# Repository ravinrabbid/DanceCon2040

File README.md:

# DanceCon2040 - A RP2040 based Dance Pad

DanceCon2040 is a firmware (and by extension a PCB) for arcade style Dance Pad controllers with up to nine panels.

It is pretty much tailored to this specific use case, if you are looking for something universal, ready-to-flash and on-the-fly configurable I'd recommend to have a look at more generic approaches like [GP2040-CE](https://github.com/OpenStickCommunity/GP2040-CE). If you however want build something more specialized or custom, feel free to use this project as a base, it is designed to be somewhat modular and should be easy remodel. See [DivaCon2040](https://github.com/ravinrabbid/DivaCon2040) or [DonCon2040](https://github.com/ravinrabbid/DonCon2040) for examples on how this could look like.
If you have any questions about the project in general or need hints how to build this thing, feel free to open a [discussion](https://github.com/ravinrabbid/DanceCon2040/discussions) anytime!

## Features

- Various controller emulation modes
  - Spice2x - Basic USB gamepad with support for HID lights
  - Xbox360 DDR - Emulates a Xbox360 DDR Dance Mat (untested!)
  - Xbox360
  - PS3 DDR - Emulates a Playstation 3 DDR Dance Mat
  - Dualshock 3
  - Dualshock 4 (Only for PC/Steam, does not work on an actual PS4!)
  - PS4 Compat - Works on PS4 (see [PS4 Authentication](#ps4-authentication) for details)
  - Switch Pro Controller
  - Keyboard - Two different mappings for player 1 or 2 available
  - Debug mode - Outputs current state via USB serial and allows direct flashing
- Support for either 4,5,6,8 or 9 panels for different games/game modes.
- Additional buttons via external i2c GPIO expander
- Basic configuration via on-screen menu on attached OLED screen
- WS2812 LED for panel illumination
- Steps-per-minute counter counter on display

## Building

<!-- I highly recommend to build the firmware yourself so you can make adjustments in `include/GlobalConfiguration.h` to match your specific controller build.
You can still use the [binary release](https://github.com/ravinrabbid/DanceCon2040/releases) which is pre-configured for the [DanceConIO](/pcb/DanceConIO). -->

### VSCode (Windows, Linux, MacOS)

Install [VSCode](https://code.visualstudio.com/) and get the [Raspberry Pi Pico](https://marketplace.visualstudio.com/items?itemName=raspberry-pi.raspberry-pi-pico) extension. From the extension choose 'Import Project' and select the folder where you've checked out this repository, then use 'Compile Project'.

### CLI

See [pico-sdk readme](https://github.com/raspberrypi/pico-sdk/blob/master/README.md#quick-start-your-own-project) for a list of pre-requisites.

Use the environment variables `PICO_SDK_PATH` to use a local pico-sdk, and `PICO_BOARD` to select another target board.
By default the pico-sdk will be fetched from Github and the target board will be "pico".

```sh
mkdir build && cd build
cmake ..
make
```

## Configuration

Few things which you probably want to change more regularly can be changed using an on-screen menu on the attached OLED display, hold both Start and Select for 2 seconds to enter the menu:

- Controller emulation mode
- Trigger thresholds
- Hold Time
- Hysteresis
- Calibration
- LED brightness, animation style and colors
- Reset settings to defaults
- Enter BOOTSEL mode for firmware flashing

Those settings are persisted to flash memory if you choose 'Save' when exiting the Menu and will survive power cycles.

Defaults and everything else is compiled statically into the firmware. You can find everything in `include/GlobalConfiguration.h`. This covers default controller emulation mode, i2c pins, ADC configuration, default trigger thresholds, hysteresis, debounce delay, panel mapping, LED colors and brightness.

### Debounce Delay / Hold Time / Hysteresis

The debounce delay also implicitly serves as the hold time of the input after a panel if triggered. On some platforms inputs won't be registered properly if this time is too short.
If you notice dropped inputs even if the controller signals an input on the LED/Display, try to increase this value.

Since the values read from load cells are not very stable, rapid triggering can happen right at the threshold value. If you encounter this, try to increase the hysteresis offset.
A panel will trigger if its value exceeds `threshold + hysteresis` and will un-trigger if its value drops below `thresholds - hysteresis` again.

### PS4 Authentication

The PS4 needs a controller to sign a cryptographic challenge every few seconds, otherwise it will stop working after around 8 minutes after plugging in. For rhythm games this is somewhat bearable, since you can re-plug the controller before starting each song to avoid running into the timeout during gameplay. Still, this is annoying.

DanceCon2040 can sign those challenges, but you will need to obtain some data from an original DS4 and compile it into the firmware. You will need a serial, signature and private key file. I can't and won't help you how to obtain those, you'll need to figure this out yourself.

To build the firmware run `scripts/generateAuthConfig.py` in the folder where you placed the required files. Copy the resulting `PS4AuthConfiguration.h` to the `include` directory, replacing the existing header. Then build the firmware as described in [Building](#building).

Signing the challenge will block the second core of the rp2040 for 2-3 seconds, so the display, external controller and LED will appear stuck from time to time. Input handling of the drum is unaffected.

## Hardware

### IO Board

The [DanceConIO](/pcb/DanceConIO) board in the pcb subfolder is built to be used with Wheatstone Bridge type panel sensors, e.g. load cells. It hosts a Waveshare RP2040-Zero and two or three ADS124S06 ADCs for up to nine differential inputs. See its [README](/pcb/DanceConIO/README.md) for details.

If you don't want to use this board, the firmware should be usable on most RP2040 boards with appropriate configuration. You may also use a more simple panel trigger solution, the firmware can also be configured to use the RP2040's internal ADC or simple GPIO style inputs.

### Controller Buttons and Display

Additional controller buttons and the display are attached to the same i2c bus. For the display, use a standard SSD1306 OLED display with 128x64 resolution. The buttons need to be attached to a MCP23017 IO expander.

See [DonConPad](/pcb/DonConPad/) for a exemplary gamepad pcb.

## Acknowledgements

- [daschr](https://github.com/daschr) for the [SSD1306 OLED driver](https://github.com/daschr/pico-ssd1306)
- [FeralAI](https://github.com/FeralAI) for the inspiration and Dualshock3/XInput driver from the [GP2040 Project](https://github.com/FeralAI/GP2040)
- The linux kernel contributors for documenting the game controllers in their drivers

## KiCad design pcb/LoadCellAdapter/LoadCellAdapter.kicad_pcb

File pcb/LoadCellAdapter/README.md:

# LoadCellAdapter

A simple passive adapter pcb to combine four 3-Wire half bridge load cells into a Wheatstone bridge configuration.

## Bill of Materials

| **Reference**      |      **Description**      | **Digikey Part** |                                                  **Notes**                                                   |
| ------------------ | :-----------------------: | :--------------: | :----------------------------------------------------------------------------------------------------------: |
| J1, J2, J3, J4, J5 | 4Pin S4B-PH-K-S Connector |   455-1721-ND    | Optional, wires can also be soldered directly to the board.</br>PHR-4 plus SPH-002T-P0.5L is the counterpart |

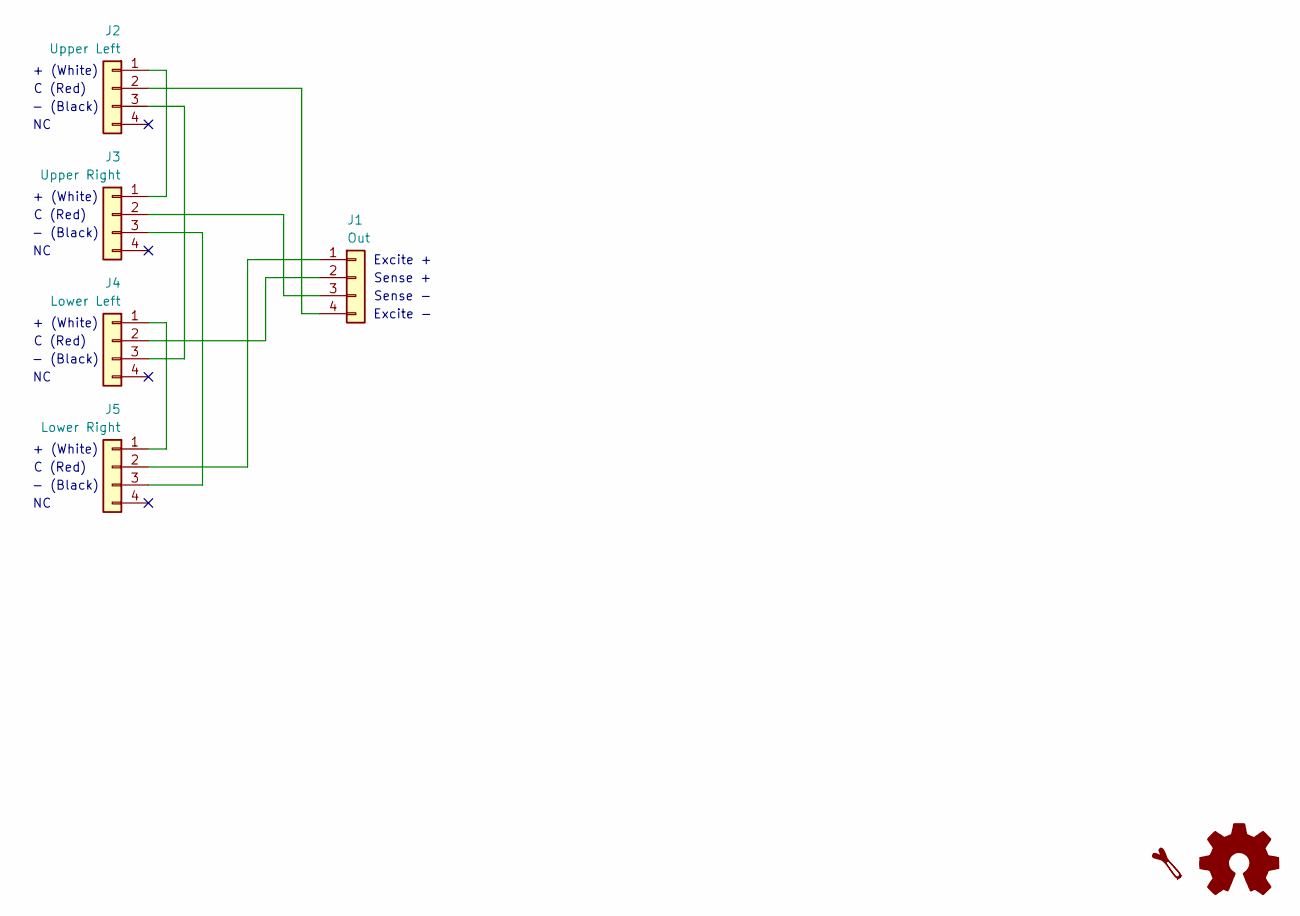
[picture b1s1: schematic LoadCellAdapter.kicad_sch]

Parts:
J1: Out; JST_PH_S4B-PH-K_1x04_P2.00mm_Horizontal
J2: Upper Left; JST_PH_S4B-PH-K_1x04_P2.00mm_Horizontal
J3: Upper Right; JST_PH_S4B-PH-K_1x04_P2.00mm_Horizontal
J4: Lower Left; JST_PH_S4B-PH-K_1x04_P2.00mm_Horizontal
J5: Lower Right; JST_PH_S4B-PH-K_1x04_P2.00mm_Horizontal

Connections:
unnamed: J1.1, J5.2
unnamed: J1.2, J4.2
unnamed: J1.3, J3.2
unnamed: J1.4, J2.2
unnamed: J2.1, J3.1
unnamed: J2.3, J4.3
unnamed: J3.3, J5.3
unnamed: J4.1, J5.1

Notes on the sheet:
+ (White)
Excite +
- (Black)
Excite -
C (Red)
Sense -
Sense +

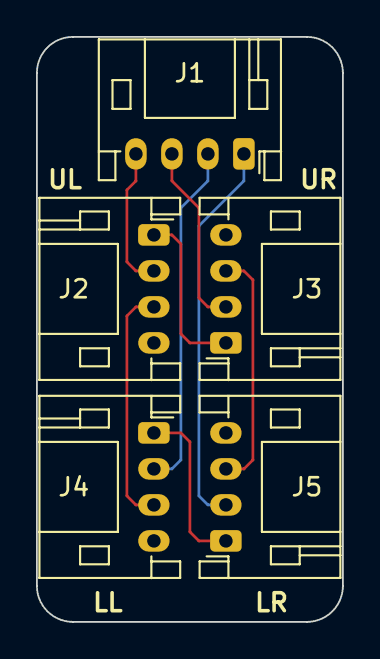
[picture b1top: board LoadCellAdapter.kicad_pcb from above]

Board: 2 copper layers, 17.0 x 32.5 mm, 5 parts (0 on the bottom side), 8 nets.

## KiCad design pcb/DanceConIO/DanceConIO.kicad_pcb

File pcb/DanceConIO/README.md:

# DanceConIO - A 9-Channel High-Speed Body Scale for the DanceCon2040

This board hosts a Waveshare RP2040-Zero microcontroller unit and provides up to 9 differential inputs for sensors in Wheatstone Bridge configuration. In addition it provides signal shitting for WS2812 style LEDs and break out connectors for I2C and GPIOs.

## Sensors

Any sensor in Wheatstone bridge configuration should work.
Tests were mainly done using a configuration of four 50kg half bridge load cells, cf. [LoadCellAdapter](../LoadCellAdapter) for wiring.
Other sensors might need adjustment of the ADC's amplifier gain within the firmware.

## Notes

- Populate either 2 or 3 of the ADC sections:
  - 4-Panel Pads need 2 ADCs.
  - 5- and 6-Panel Pads can use 2 or 3 ADCs, using 3 will increase the sample rate.
  - 8- and 9-Panel Pads need 3 ADCs.
- Populated ADCs must be configured in firmware, otherwise they will interfere with the SPI bus and prevent the other ADCs from working properly.
- If readings are too noisy you can try lowering the sample rate or using the ADC's Sinc3 filter. See table below for the example sample rates of a full scan of all panels.

### Expected Sample Rates

| Configuration<br>Filter | 2 ADCs w/ 4 Panels or 3 ADCs w/ 6 Panels ADC<br>LowLatency / Sinc3 | 2 ADCs w/ 6 Panels or 3 ADCs w/ 9 Panels ADC<br>LowLatency / Sinc3 |
| ----------------------: | :----------------------------------------------------------------: | :----------------------------------------------------------------: |
|                4000kSPS |                           1020Hz / 512Hz                           |                           680Hz / 342Hz                            |
|                2000kSPS |                           675Hz / 290Hz                            |                           450Hz / 194Hz                            |
|                1000kSPS |                           403Hz / 155Hz                            |                           270Hz / 103Hz                            |
|                 800kSPS |                           335Hz / 122Hz                            |                            223Hz / 82Hz                            |
|                 400kSPS |                            182Hz / 64Hz                            |                            122Hz / 42Hz                            |
|                 200kSPS |                            95Hz / 32Hz                             |                            63Hz / 22Hz                             |
|                 100kSPS |                            48Hz / 16Hz                             |                              32Hz / -                              |

## Bill of Materials

| **Reference**                                                                                                       |                **Description**                |      **Digikey Part**       |                                **Notes**                                 |
| ------------------------------------------------------------------------------------------------------------------- | :-------------------------------------------: | :-------------------------: | :----------------------------------------------------------------------: |
| U1                                                                                                                  | 74LVC1T45 Dual supply translating transceiver |       1727-4560-1-ND        | Can be omitted if you don't need level shifting, bridge JP1 in this case |
| U2                                                                                                                  |             Waveshare RP2040-Zero             |              -              |                                                                          |
| U3, U4, U5                                                                                                          |        ADS124S06 24bit Delta-Sigma ADC        |       296-45169-1-ND        |                                                                          |
| C1, C2, C4, C19, C34                                                                                                |          0.1µF SMD Ceramic Capacitor          |       1276-1003-1-ND        |                                                                          |
| C3, C18, C33                                                                                                        |          330nF SMD Ceramic Capacitor          |       1276-1123-1-ND        |                                                                          |
| C5, C20, C35                                                                                                        |           1µF SMD Ceramic Capacitor           |       1276-1029-1-ND        |                                                                          |
| C6, C8, C9, C11, C12, C14, C15, C17, C21, C23, C24, C26, C27, C29, C30, C32, C36, C38, C39, C41, C42, C44, C45, C47 |      2.2nF C0G/NP0 SMD Ceramic Capacitor      |       1276-2993-1-ND        |                                                                          |
| C7, C10, C13, C16, C22, C25, C28, C31, C37, C40, C43, C46                                                           |      22nF C0G/NP0 SMD Ceramic Capacitor       | 490-GRM2165C1H223JA01DCT-ND |                                                                          |
| R1-R9                                                                                                               |               47Ω SMD Resistor                |  2019-RK73H2ATTD47R0FCT-ND  |                                                                          |
| R10-R17, R19-R26, R28-R35                                                                                           |               150Ω SMD Resistor               |  2019-RK73H2ATTD1500FCT-ND  |                                                                          |
| R18, R27, R36                                                                                                       |              100kΩ SMD Resistor               |  2019-RK73H2ATTD1003FCT-ND  |                                                                          |
| J1-J12                                                                                                              |           4Pin S5B-PH-K-S Connector           |         455-1721-ND         |               PHR-4 plus SPH-002T-P0.5L is the counterpart               |

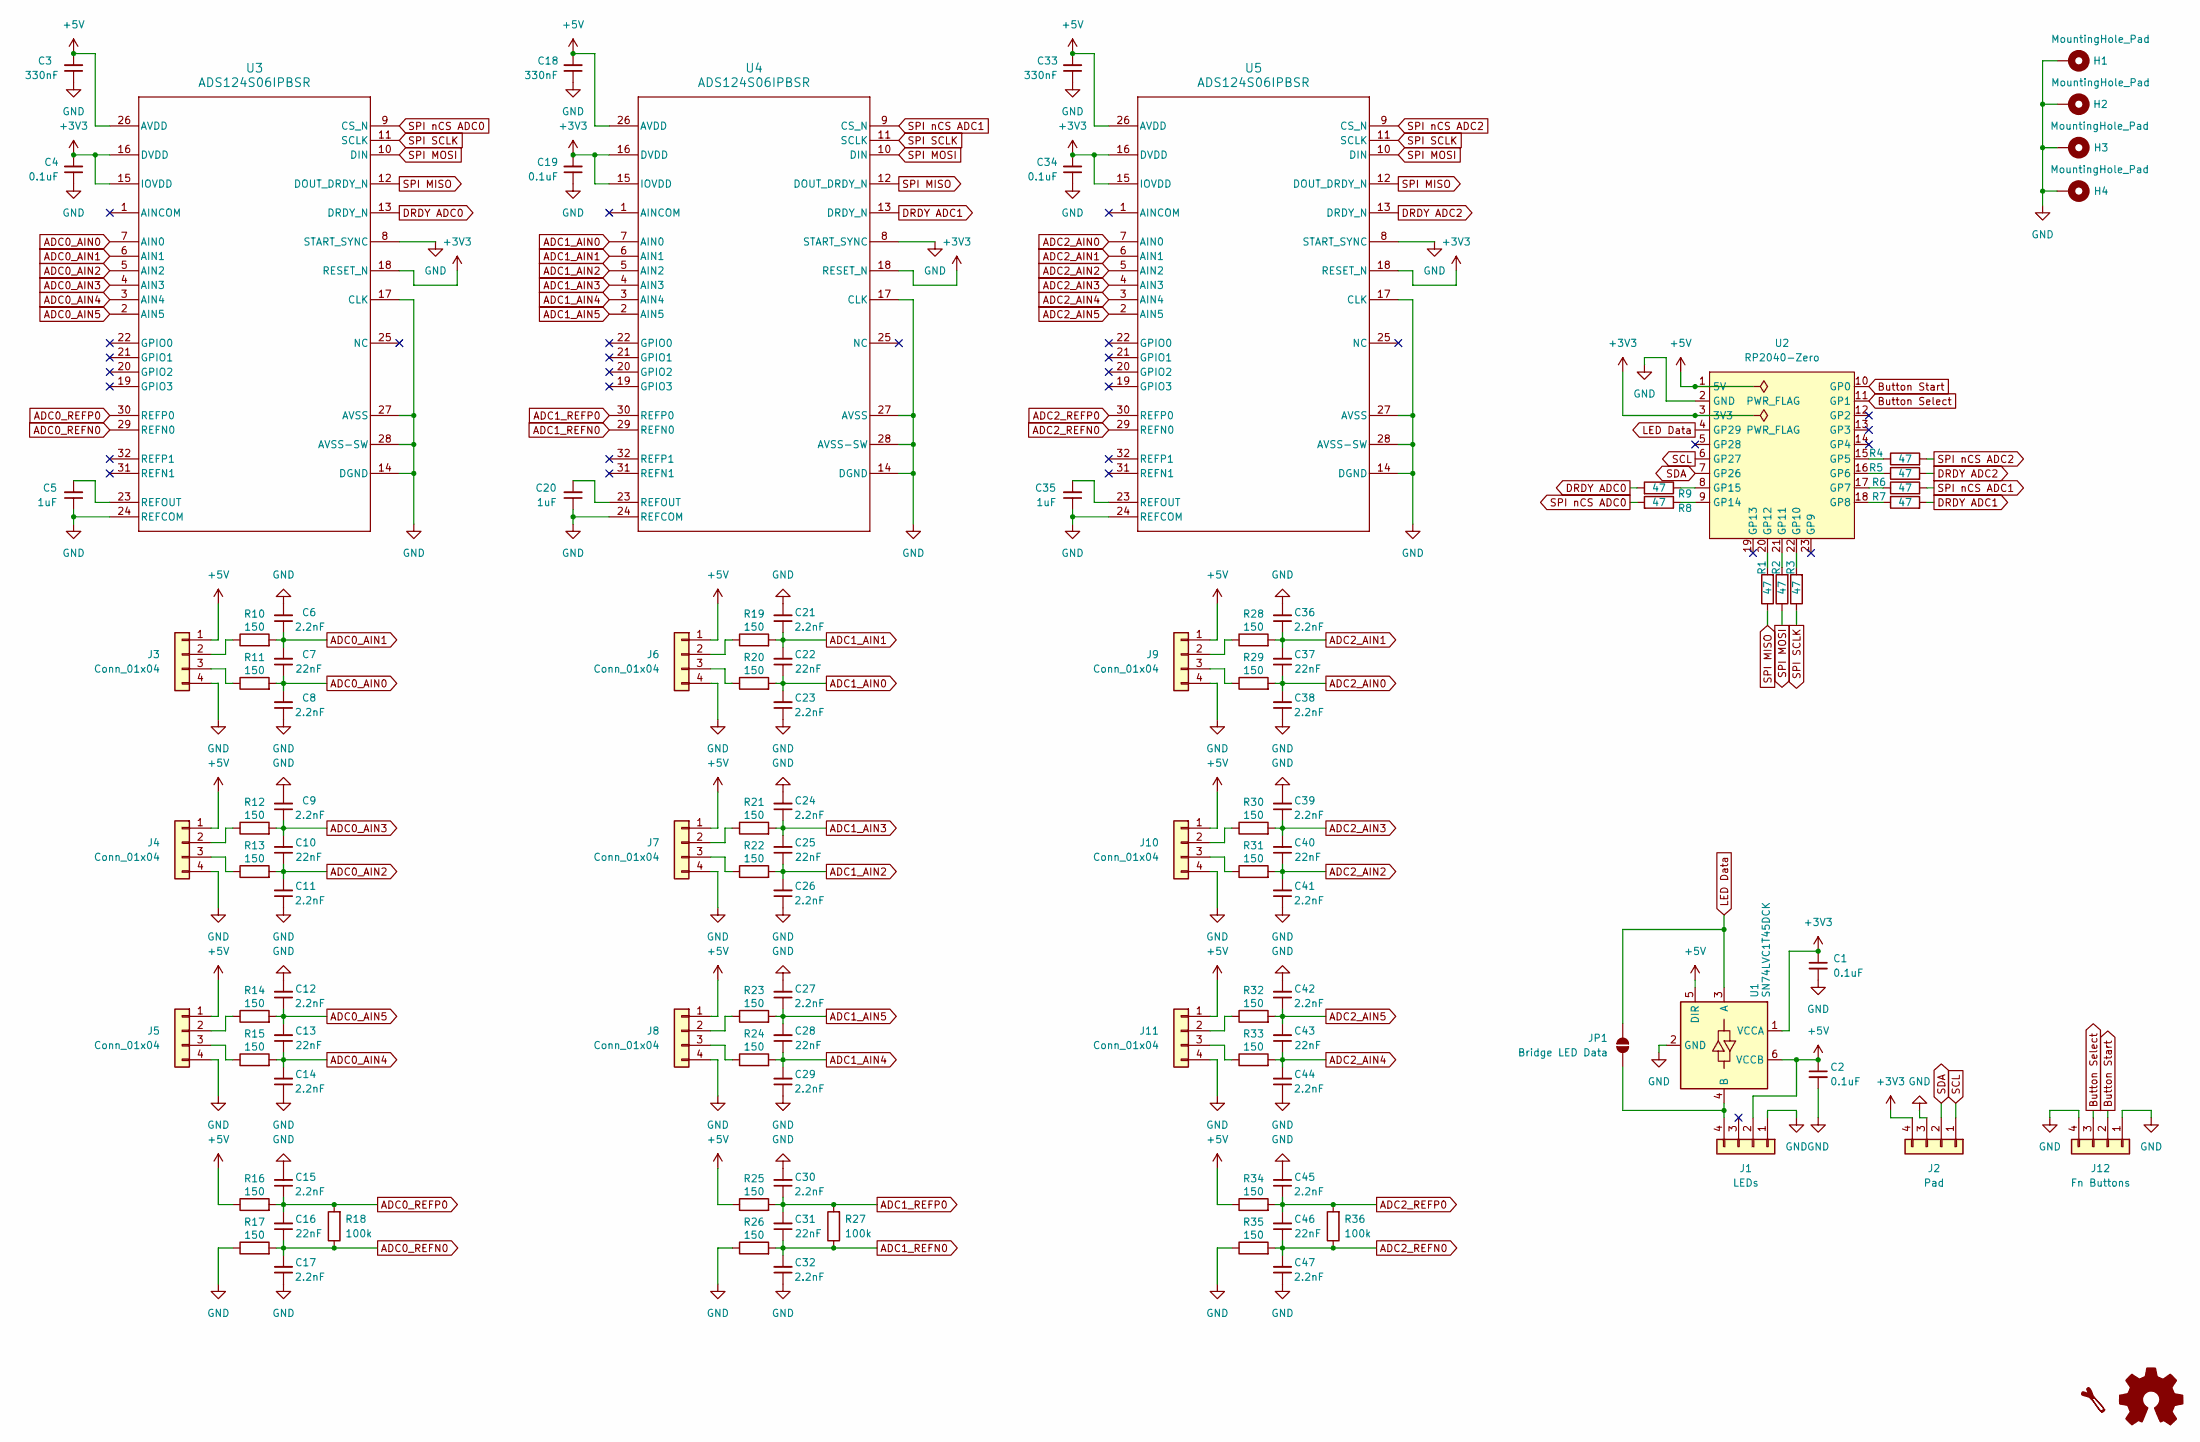
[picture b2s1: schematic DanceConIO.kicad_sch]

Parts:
C1, C2, C4, C19, C34: 0.1uF; C_0805_2012Metric_Pad1.18x1.45mm_HandSolder
C3, C18, C33: 330nF; C_0805_2012Metric_Pad1.18x1.45mm_HandSolder
C5, C20, C35: 1uF; C_0805_2012Metric_Pad1.18x1.45mm_HandSolder
C6, C8, C9, C11, C12, C14, C15, C17, C21, C23, C24, C26, C27, C29, C30, C32, C36, C38, C39, C41, C42, C44, C45, C47: 2.2nF; C_0805_2012Metric_Pad1.18x1.45mm_HandSolder
C7, C10, C13, C16, C22, C25, C28, C31, C37, C40, C43, C46: 22nF; C_0805_2012Metric_Pad1.18x1.45mm_HandSolder
H1, H2, H3, H4: MountingHole_Pad; MountingHole_4.5mm_Pad_TopOnly
J1: LEDs; JST_PH_S4B-PH-K_1x04_P2.00mm_Horizontal
J2: Pad; JST_PH_S4B-PH-K_1x04_P2.00mm_Horizontal
J3, J4, J5, J6, J7, J8, J9, J10, J11: Conn_01x04; JST_PH_S4B-PH-K_1x04_P2.00mm_Horizontal
J12: Fn Buttons; JST_PH_S4B-PH-K_1x04_P2.00mm_Horizontal
JP1: Bridge LED Data; SolderJumper-2_P1.3mm_Open_RoundedPad1.0x1.5mm
R1, R2, R3, R4, R5, R6, R7, R8, R9: 47; R_0805_2012Metric_Pad1.20x1.40mm_HandSolder
R10, R11, R12, R13, R14, R15, R16, R17, R19, R20, R21, R22, R23, R24, R25, R26, R28, R29, R30, R31, R32, R33, R34, R35: 150; R_0805_2012Metric_Pad1.20x1.40mm_HandSolder
R18, R27, R36: 100k; R_0805_2012Metric_Pad1.20x1.40mm_HandSolder
U1: SN74LVC1T45DCK; SOT-363_SC-70-6_Handsoldering
U2: RP2040-Zero; RP2040 Zero
U3, U4, U5: ADS124S06IPBSR; PQFP-32_5x5mm_P0.5mm

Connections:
+3V3: C1.1, C4.2, C19.2, C34.2, J2.4, U1.1 (VCCA), U2.3 (3V3), U3.15 (IOVDD), U3.16 (DVDD), U3.18 (RESET_N), U4.15 (IOVDD), U4.16 (DVDD), U4.18 (RESET_N), U5.15 (IOVDD), U5.16 (DVDD), U5.18 (RESET_N)
+5V: C2.1, C3.2, C18.2, C33.2, J1.2, J3.1, J4.1, J5.1, J6.1, J7.1, J8.1, J9.1, J10.1, J11.1, R16.1, R25.1, R34.1, U1.5 (DIR), U1.6 (VCCB), U2.1 (5V), U3.26 (AVDD), U4.26 (AVDD), U5.26 (AVDD)
ADC0_AIN0: C7.1, C8.2, R11.2, U3.7 (AIN0)
ADC0_AIN1: C6.1, C7.2, R10.2, U3.6 (AIN1)
ADC0_AIN2: C10.1, C11.2, R13.2, U3.5 (AIN2)
ADC0_AIN3: C9.1, C10.2, R12.2, U3.4 (AIN3)
ADC0_AIN4: C13.1, C14.2, R15.2, U3.3 (AIN4)
ADC0_AIN5: C12.1, C13.2, R14.2, U3.2 (AIN5)
ADC0_REFN0: C16.1, C17.2, R17.2, R18.1, U3.29 (REFN0)
ADC0_REFP0: C15.1, C16.2, R16.2, R18.2, U3.30 (REFP0)
ADC1_AIN0: C22.1, C23.2, R20.2, U4.7 (AIN0)
ADC1_AIN1: C21.1, C22.2, R19.2, U4.6 (AIN1)
ADC1_AIN2: C25.1, C26.2, R22.2, U4.5 (AIN2)
ADC1_AIN3: C24.1, C25.2, R21.2, U4.4 (AIN3)
ADC1_AIN4: C28.1, C29.2, R24.2, U4.3 (AIN4)
ADC1_AIN5: C27.1, C28.2, R23.2, U4.2 (AIN5)
ADC1_REFN0: C31.1, C32.2, R26.2, R27.1, U4.29 (REFN0)
ADC1_REFP0: C30.1, C31.2, R25.2, R27.2, U4.30 (REFP0)
ADC2_AIN0: C37.1, C38.2, R29.2, U5.7 (AIN0)
ADC2_AIN1: C36.1, C37.2, R28.2, U5.6 (AIN1)
ADC2_AIN2: C40.1, C41.2, R31.2, U5.5 (AIN2)
ADC2_AIN3: C39.1, C40.2, R30.2, U5.4 (AIN3)
ADC2_AIN4: C43.1, C44.2, R33.2, U5.3 (AIN4)
ADC2_AIN5: C42.1, C43.2, R32.2, U5.2 (AIN5)
ADC2_REFN0: C46.1, C47.2, R35.2, R36.1, U5.29 (REFN0)
ADC2_REFP0: C45.1, C46.2, R34.2, R36.2, U5.30 (REFP0)
Button Select: J12.3, U2.11 (GP1)
Button Start: J12.2, U2.10 (GP0)
DRDY ADC0: R9.2, U3.13 (DRDY_N)
DRDY ADC1: R7.2, U4.13 (DRDY_N)
DRDY ADC2: R5.2, U5.13 (DRDY_N)
GND: C1.2, C2.2, C3.1, C4.1, C5.1, C6.2, C8.1, C9.2, C11.1, C12.2, C14.1, C15.2, C17.1, C18.1, C19.1, C20.1, C21.2, C23.1, C24.2, C26.1, C27.2, C29.1, C30.2, C32.1, C33.1, C34.1, C35.1, C36.2, C38.1, C39.2, C41.1, C42.2, C44.1, C45.2, C47.1, H1.1, H2.1, H3.1, H4.1, J1.1, J2.3, J3.4, J4.4, J5.4, J6.4, J7.4, J8.4, J9.4, J10.4, J11.4, J12.1, J12.4, R17.1, R26.1, R35.1, U1.2 (GND), U2.2 (GND), U3.8 (START_SYNC), U3.14 (DGND), U3.17 (CLK), U3.24 (REFCOM), U3.27 (AVSS), U3.28 (AVSS-SW), U4.8 (START_SYNC), U4.14 (DGND), U4.17 (CLK), U4.24 (REFCOM), U4.27 (AVSS), U4.28 (AVSS-SW), U5.8 (START_SYNC), U5.14 (DGND), U5.17 (CLK), U5.24 (REFCOM), U5.27 (AVSS), U5.28 (AVSS-SW)
LED Data: JP1.1 (A), U1.3 (A), U2.4 (GP29)
unnamed: J1.4, JP1.2 (B), U1.4 (B)
unnamed: J3.2, R10.1
unnamed: J3.3, R11.1
unnamed: J4.2, R12.1
unnamed: J4.3, R13.1
unnamed: J5.2, R14.1
unnamed: J5.3, R15.1
unnamed: J6.2, R19.1
unnamed: J6.3, R20.1
unnamed: J7.2, R21.1
unnamed: J7.3, R22.1
unnamed: J8.2, R23.1
unnamed: J8.3, R24.1
unnamed: J9.2, R28.1
unnamed: J9.3, R29.1
unnamed: J10.2, R30.1
unnamed: J10.3, R31.1
unnamed: J11.2, R32.1
unnamed: J11.3, R33.1
unnamed: R4.1, U2.15 (GP5)
unnamed: R5.1, U2.16 (GP6)
unnamed: R6.1, U2.17 (GP7)
unnamed: R7.1, U2.18 (GP8)
unnamed: R3.2, U2.22 (GP10)
unnamed: R2.2, U2.21 (GP11)
unnamed: R1.2, U2.20 (GP12)
unnamed: R8.1, U2.9 (GP14)
unnamed: R9.1, U2.8 (GP15)
unnamed: C5.2, U3.23 (REFOUT)
unnamed: C20.2, U4.23 (REFOUT)
unnamed: C35.2, U5.23 (REFOUT)
SCL: J2.1, U2.6 (GP27)
SDA: J2.2, U2.7 (GP26)
SPI MISO: R1.1, U3.12 (DOUT_DRDY_N), U4.12 (DOUT_DRDY_N), U5.12 (DOUT_DRDY_N)
SPI MOSI: R2.1, U3.10 (DIN), U4.10 (DIN), U5.10 (DIN)
SPI SCLK: R3.1, U3.11 (SCLK), U4.11 (SCLK), U5.11 (SCLK)
SPI nCS ADC0: R8.2, U3.9 (CS_N)
SPI nCS ADC1: R6.2, U4.9 (CS_N)
SPI nCS ADC2: R4.2, U5.9 (CS_N)

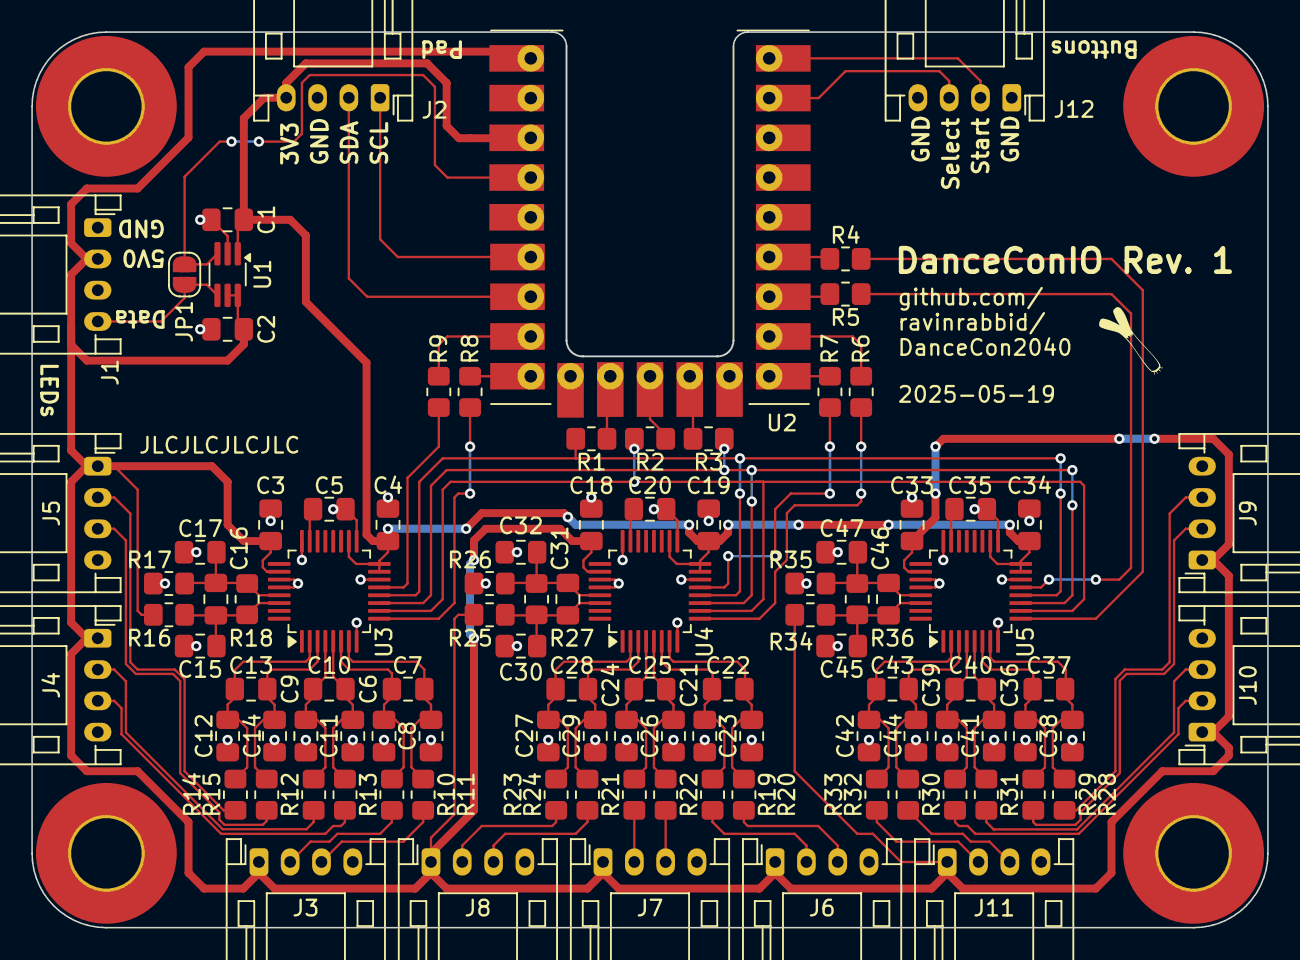
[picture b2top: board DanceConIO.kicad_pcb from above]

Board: 2 copper layers, 79.0 x 57.2 mm, 105 parts (0 on the bottom side), 72 nets.

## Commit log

2025-04-20 Boostrap project
2025-09-16 Add DanceConIO pcb
2025-09-16 Add Pad Buttons
2025-09-16 Add pad calibration
2025-09-16 Add BPM counter
2025-09-16 Add panel illumination
2025-09-16 Read panel load cells
2025-09-16 Add library for ADS124S0x
2025-09-16 Add Display and Menu
2025-09-16 Add LoadCellAdapter PCB
2025-09-16 Add support for internal ADC
2025-09-16 Add support for on-board status led
2025-09-17 Remove MIDI mode
2025-09-17 Add Xbox360 Dance Pad support
2025-09-17 Add PS3 Dance Mat support
2025-09-17 Set keyboard mode keybinds
2025-09-18 Add button mappings for remaining modes
2025-09-18 Add support to use GPIOs as pad inputs
2025-09-19 Add Spice2x Mode
2025-09-19 Add DanceConIO readme
2025-09-20 Add examples to GlobalConfiguration
2025-09-20 Add README
2025-09-21 Decouple Panel and PanelLed count
2025-09-21 Add sample rate measurements
2025-09-21 Expose status led via HID lights
2025-09-21 Expose ADC sample rate, gain and filter in config
2025-09-22 Add hysteresis for panel triggers
2025-09-24 clang-tidy lint
2025-09-25 Fix PS3 Dance Pad mode
2025-09-25 Refactor InputState
2025-09-28 refactor: remove static variables in members
2025-10-02 Draw pad state on display
2025-10-02 Add oversampling for all ADC types
2025-10-02 Add scale feature
